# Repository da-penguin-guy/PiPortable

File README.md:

# PiPortable

This is a project that is designed to shove a CM5, a huge battery, and the pi touchscreen into a handheld form-factor. This is meant to help with troubleshooting for audio engineers, although the code is being designed to be very open, allowing you to add your own apps to the launcher and create custom IO Cards

# Source Code
The code can be found in the folder labeled "Source Code." Good luck.

# PCB Design Files
¯\_(ツ)_/¯

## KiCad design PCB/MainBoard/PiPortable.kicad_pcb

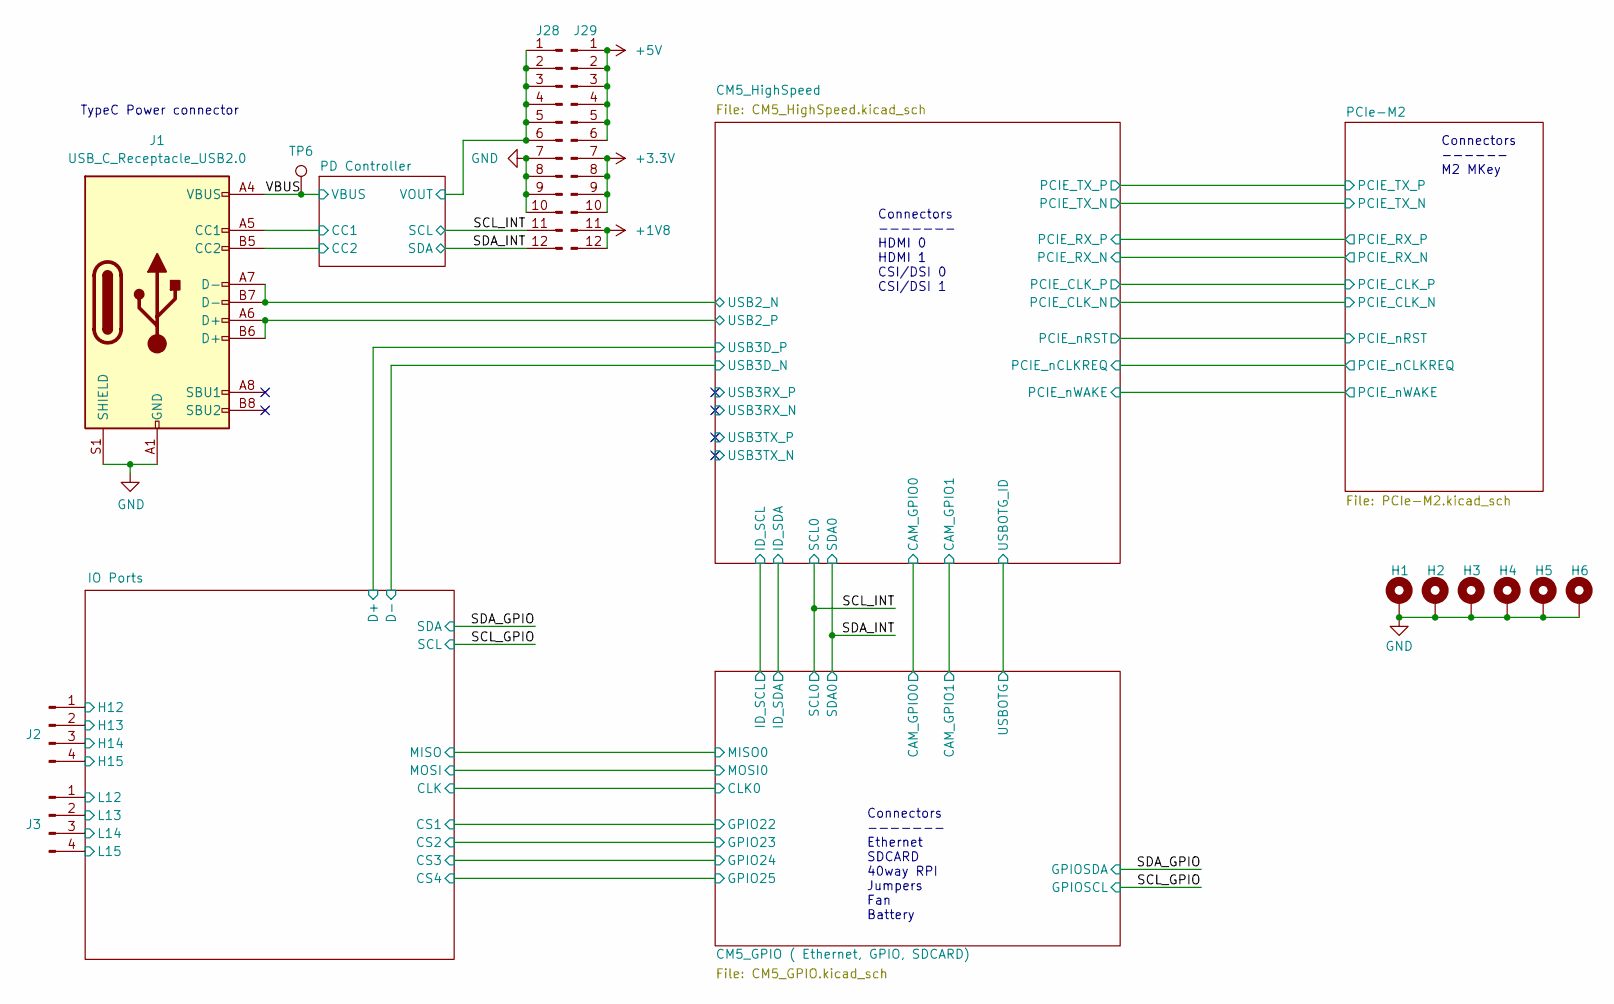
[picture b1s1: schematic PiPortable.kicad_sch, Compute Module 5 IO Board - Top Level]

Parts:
H1, H2, H3, H4, H5, H6: MountingHole_Pad; MountingHole_2.7mm_M2.5_DIN965_Pad
J1: USB_C_Receptacle_USB2.0; USB_C_Receptacle_Amphenol_12401548E4-2A; Part Description USBC USB2 data and power connector
J2, J3: Conn_01x04_Pin; PinHeader_1x04_P1.27mm_Vertical
J28, J29: Conn_01x12_Pin; PinHeader_1x12_P1.27mm_Vertical
TP6: TestPoint; TestPoint_Pad_D3.0mm

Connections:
+1V8: J29.11, J29.12; also elsewhere on the board
+3.3V: J29.7, J29.8, J29.9, J29.10; also elsewhere on the board
+5V: J29.1, J29.2, J29.3, J29.4, J29.5, J29.6; also elsewhere on the board
/CM5_HighSpeed/USB2_N: J1.A7 (D-), J1.B7 (D-); also elsewhere on the board
/CM5_HighSpeed/USB2_P: J1.A6 (D+), J1.B6 (D+); also elsewhere on the board
/IO Ports/H12: J2.1; also elsewhere on the board
/IO Ports/H13: J2.2; also elsewhere on the board
/IO Ports/H14: J2.3; also elsewhere on the board
/IO Ports/H15: J2.4; also elsewhere on the board
/IO Ports/L12: J3.1; also elsewhere on the board
/IO Ports/L13: J3.2; also elsewhere on the board
/IO Ports/L14: J3.3; also elsewhere on the board
/IO Ports/L15: J3.4; also elsewhere on the board
/PD Controller/CC1: J1.A5 (CC1); also elsewhere on the board
/PD Controller/CC2: J1.B5 (CC2); also elsewhere on the board
/PD Controller/VOUT: J28.1, J28.2, J28.3, J28.4, J28.5, J28.6; also elsewhere on the board
/SCL_INT: J28.11; also elsewhere on the board
/SDA_INT: J28.12; also elsewhere on the board
/VBUS: J1.A4 (VBUS), J1.A9 (VBUS), J1.B4 (VBUS), J1.B9 (VBUS), TP6.1; also elsewhere on the board
GND: H1.1, H2.1, H3.1, H4.1, H5.1, H6.1, J1.A1 (GND), J1.A12 (GND), J1.B1 (GND), J1.B12 (GND), J1.S1 (SHIELD), J28.7, J28.8, J28.9, J28.10; also elsewhere on the board

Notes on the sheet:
Connectors ------- Ethernet SDCARD 40way RPI Jumpers Fan Battery
Connectors ------ M2 MKey
TypeC Power connector
Connectors ------- HDMI 0 HDMI 1 CSI/DSI 0 CSI/DSI 1

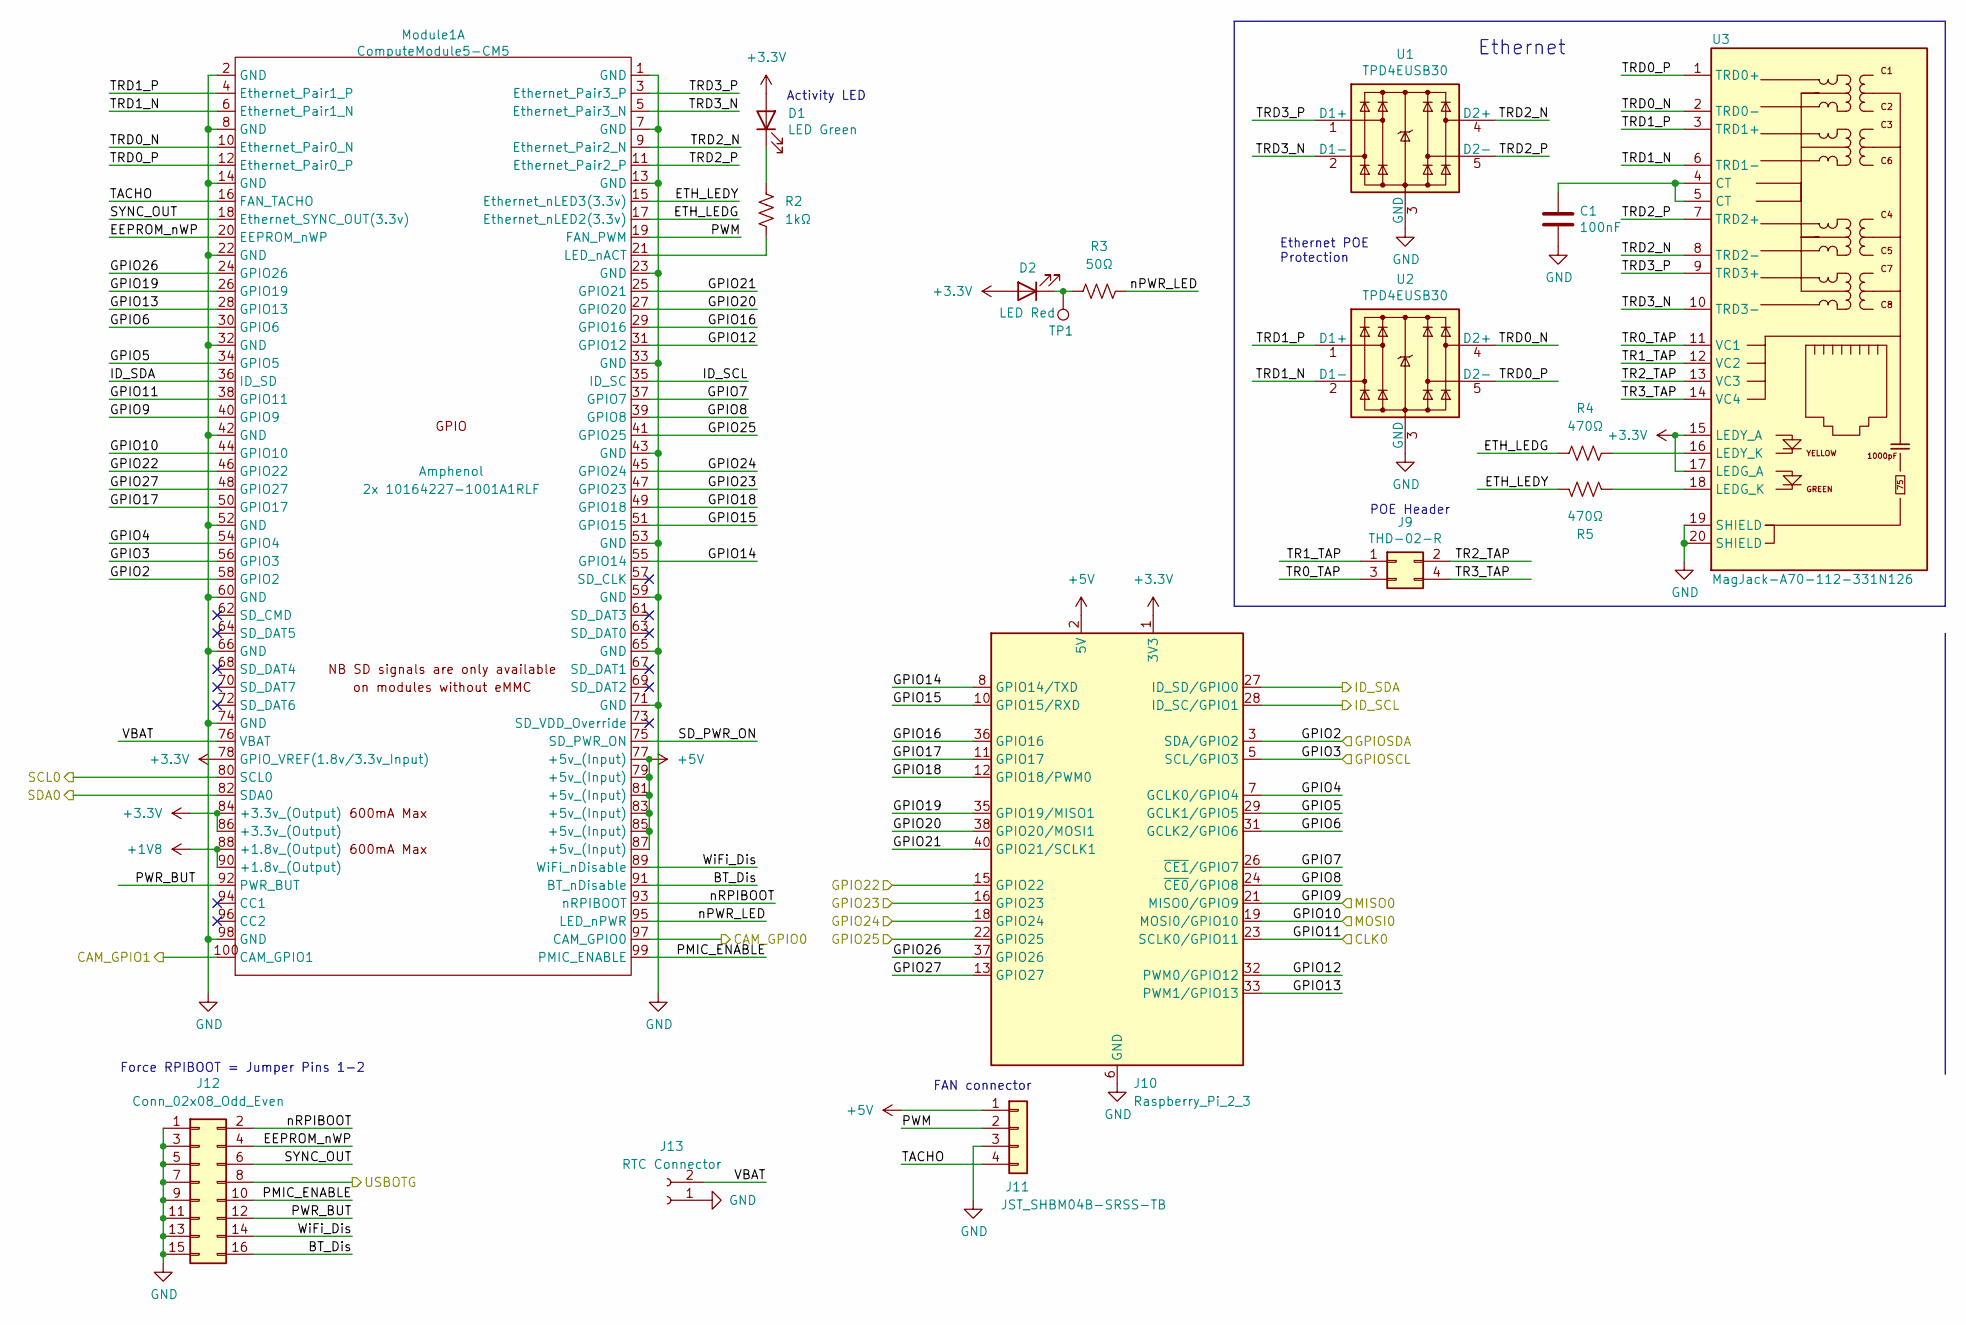
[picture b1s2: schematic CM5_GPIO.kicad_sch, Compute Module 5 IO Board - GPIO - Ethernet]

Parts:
C1: 100nF; C_0402_1005Metric_Pad0.74x0.62mm_HandSolder; Part Description 0.1uF 10% 16V Ceramic Capacitor X7R 040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
D1: LED Green; LED_0603_1608Metric; Part Description Green 572nm LED Indication - Discrete 2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
D2: LED Red; LED_0603_1608Metric; Part Description Red 620nm LED Indication - Discrete 2.2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
J9: THD-02-R; PinHeader_2x02_P2.54mm_Vertical; Part Description PinHeader_2x02_P2.54mm_Vertical
J10: Raspberry_Pi_2_3; PinHeader_2x20_P2.54mm_Vertical
J11: JST_SHBM04B-SRSS-TB; JST_SH_BM04B-SRSS-TB_1x04-1MP_P1.00mm_Vertical; Part Description 4 pin vertical 1mm pitch connector
J12: Conn_02x08_Odd_Even; PinHeader_2x08_P1.27mm_Vertical
J13: RTC Connector; JST_EH_B2B-EH-A_1x02_P2.50mm_Vertical
Module1: ComputeModule5-CM5; Raspberry-Pi-5-Compute-Module; Part Description 100 Position Connector Receptacle, Cent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
R2: 1kΩ; R_0402_1005Metric_Pad0.72x0.64mm_HandSolder
R3: 50Ω; R_0402_1005Metric_Pad0.72x0.64mm_HandSolder
R4, R5: 470Ω; R_0402_1005Metric_Pad0.72x0.64mm_HandSolder
TP1: TestPoint; TestPoint_Pad_2.0x2.0mm; Part Description Test point
U1, U2: TPD4EUSB30; USON-10_2.5x1.0mm_P0.5mm; Part Description Quad TVS diode for high speed signals (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
U3: MagJack-A70-112-331N126; TRJG0926HENL; Part Description Gigabit Ethernet Magjack

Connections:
+1V8: Module1.88 (+1.8v_(Output)), Module1.90 (+1.8v_(Output)); also elsewhere on the board
+3.3V: D1.2 (A), D2.2 (A), J10.1 (3V3), J10.17 (3V3), Module1.78 (GPIO_VREF(1.8v/3.3v_Input)), Module1.84 (+3.3v_(Output)), Module1.86 (+3.3v_(Output)), U3.15 (LEDY_A), U3.17 (LEDG_A); also elsewhere on the board
+5V: J10.2 (5V), J10.4 (5V), J11.1, Module1.77 (+5v_(Input)), Module1.79 (+5v_(Input)), Module1.81 (+5v_(Input)), Module1.83 (+5v_(Input)), Module1.85 (+5v_(Input)), Module1.87 (+5v_(Input)); also elsewhere on the board
/CM5_GPIO ( Ethernet, GPIO, SDCARD)/BT_Dis: J12.16, Module1.91 (BT_nDisable)
/CM5_GPIO ( Ethernet, GPIO, SDCARD)/CAM_GPIO0: Module1.97 (CAM_GPIO0); also elsewhere on the board
/CM5_GPIO ( Ethernet, GPIO, SDCARD)/CAM_GPIO1: Module1.100 (CAM_GPIO1); also elsewhere on the board
/CM5_GPIO ( Ethernet, GPIO, SDCARD)/EEPROM_nWP: J12.4, Module1.20 (EEPROM_nWP)
/CM5_GPIO ( Ethernet, GPIO, SDCARD)/ETH_LEDG: Module1.17 (Ethernet_nLED2(3.3v)), R4.1
/CM5_GPIO ( Ethernet, GPIO, SDCARD)/ETH_LEDY: Module1.15 (Ethernet_nLED3(3.3v)), R5.1
/CM5_GPIO ( Ethernet, GPIO, SDCARD)/GPIO4: J10.7 (GCLK0/GPIO4), Module1.54 (GPIO4)
/CM5_GPIO ( Ethernet, GPIO, SDCARD)/GPIO5: J10.29 (GCLK1/GPIO5), Module1.34 (GPIO5)
/CM5_GPIO ( Ethernet, GPIO, SDCARD)/GPIO6: J10.31 (GCLK2/GPIO6), Module1.30 (GPIO6)
/CM5_GPIO ( Ethernet, GPIO, SDCARD)/GPIO7: J10.26 (~CE1/GPIO7), Module1.37 (GPIO7)
/CM5_GPIO ( Ethernet, GPIO, SDCARD)/GPIO8: J10.24 (~CE0/GPIO8), Module1.39 (GPIO8)
/CM5_GPIO ( Ethernet, GPIO, SDCARD)/GPIO9: J10.21 (MISO0/GPIO9), Module1.40 (GPIO9); also elsewhere on the board
/CM5_GPIO ( Ethernet, GPIO, SDCARD)/GPIO10: J10.19 (MOSI0/GPIO10), Module1.44 (GPIO10); also elsewhere on the board
/CM5_GPIO ( Ethernet, GPIO, SDCARD)/GPIO11: J10.23 (SCLK0/GPIO11), Module1.38 (GPIO11); also elsewhere on the board
/CM5_GPIO ( Ethernet, GPIO, SDCARD)/GPIO12: J10.32 (PWM0/GPIO12), Module1.31 (GPIO12)
/CM5_GPIO ( Ethernet, GPIO, SDCARD)/GPIO13: J10.33 (PWM1/GPIO13), Module1.28 (GPIO13)
/CM5_GPIO ( Ethernet, GPIO, SDCARD)/GPIO14: J10.8 (GPIO14/TXD), Module1.55 (GPIO14)
/CM5_GPIO ( Ethernet, GPIO, SDCARD)/GPIO15: J10.10 (GPIO15/RXD), Module1.51 (GPIO15)
/CM5_GPIO ( Ethernet, GPIO, SDCARD)/GPIO16: J10.36 (GPIO16), Module1.29 (GPIO16)
/CM5_GPIO ( Ethernet, GPIO, SDCARD)/GPIO17: J10.11 (GPIO17), Module1.50 (GPIO17)
/CM5_GPIO ( Ethernet, GPIO, SDCARD)/GPIO18: J10.12 (GPIO18/PWM0), Module1.49 (GPIO18)
/CM5_GPIO ( Ethernet, GPIO, SDCARD)/GPIO19: J10.35 (GPIO19/MISO1), Module1.26 (GPIO19)
/CM5_GPIO ( Ethernet, GPIO, SDCARD)/GPIO20: J10.38 (GPIO20/MOSI1), Module1.27 (GPIO20)
/CM5_GPIO ( Ethernet, GPIO, SDCARD)/GPIO21: J10.40 (GPIO21/SCLK1), Module1.25 (GPIO21)
/CM5_GPIO ( Ethernet, GPIO, SDCARD)/GPIO22: J10.15 (GPIO22), Module1.46 (GPIO22); also elsewhere on the board
/CM5_GPIO ( Ethernet, GPIO, SDCARD)/GPIO23: J10.16 (GPIO23), Module1.47 (GPIO23); also elsewhere on the board
/CM5_GPIO ( Ethernet, GPIO, SDCARD)/GPIO24: J10.18 (GPIO24), Module1.45 (GPIO24); also elsewhere on the board
/CM5_GPIO ( Ethernet, GPIO, SDCARD)/GPIO25: J10.22 (GPIO25), Module1.41 (GPIO25); also elsewhere on the board
/CM5_GPIO ( Ethernet, GPIO, SDCARD)/GPIO26: J10.37 (GPIO26), Module1.24 (GPIO26)
/CM5_GPIO ( Ethernet, GPIO, SDCARD)/GPIO27: J10.13 (GPIO27), Module1.48 (GPIO27)
/CM5_GPIO ( Ethernet, GPIO, SDCARD)/ID_SCL: J10.28 (ID_SC/GPIO1), Module1.35 (ID_SC)
/CM5_GPIO ( Ethernet, GPIO, SDCARD)/ID_SDA: J10.27 (ID_SD/GPIO0), Module1.36 (ID_SD)
/CM5_GPIO ( Ethernet, GPIO, SDCARD)/PMIC_ENABLE: J12.10, Module1.99 (PMIC_ENABLE)
/CM5_GPIO ( Ethernet, GPIO, SDCARD)/PWM: J11.2, Module1.19 (FAN_PWM)
/CM5_GPIO ( Ethernet, GPIO, SDCARD)/PWR_BUT: J12.12, Module1.92 (PWR_BUT)
/CM5_GPIO ( Ethernet, GPIO, SDCARD)/SD_PWR_ON: Module1.75 (SD_PWR_ON)
/CM5_GPIO ( Ethernet, GPIO, SDCARD)/SYNC_OUT: J12.6, Module1.18 (Ethernet_SYNC_OUT(3.3v))
/CM5_GPIO ( Ethernet, GPIO, SDCARD)/TACHO: J11.4, Module1.16 (FAN_TACHO)
/CM5_GPIO ( Ethernet, GPIO, SDCARD)/TR0_TAP: J9.3, U3.11 (VC1)
/CM5_GPIO ( Ethernet, GPIO, SDCARD)/TR1_TAP: J9.1, U3.12 (VC2)
/CM5_GPIO ( Ethernet, GPIO, SDCARD)/TR2_TAP: J9.2, U3.13 (VC3)
/CM5_GPIO ( Ethernet, GPIO, SDCARD)/TR3_TAP: J9.4, U3.14 (VC4)
/CM5_GPIO ( Ethernet, GPIO, SDCARD)/TRD0_N: Module1.10 (Ethernet_Pair0_N), U2.4 (D2+), U2.7, U3.2 (TRD0-)
/CM5_GPIO ( Ethernet, GPIO, SDCARD)/TRD0_P: Module1.12 (Ethernet_Pair0_P), U2.5 (D2-), U2.6, U3.1 (TRD0+)
/CM5_GPIO ( Ethernet, GPIO, SDCARD)/TRD1_N: Module1.6 (Ethernet_Pair1_N), U2.2 (D1-), U2.9, U3.6 (TRD1-)
/CM5_GPIO ( Ethernet, GPIO, SDCARD)/TRD1_P: Module1.4 (Ethernet_Pair1_P), U2.1 (D1+), U2.10, U3.3 (TRD1+)
/CM5_GPIO ( Ethernet, GPIO, SDCARD)/TRD2_N: Module1.9 (Ethernet_Pair2_N), U1.4 (D2+), U1.7, U3.8 (TRD2-)
/CM5_GPIO ( Ethernet, GPIO, SDCARD)/TRD2_P: Module1.11 (Ethernet_Pair2_P), U1.5 (D2-), U1.6, U3.7 (TRD2+)
/CM5_GPIO ( Ethernet, GPIO, SDCARD)/TRD3_N: Module1.5 (Ethernet_Pair3_N), U1.2 (D1-), U1.9, U3.10 (TRD3-)
/CM5_GPIO ( Ethernet, GPIO, SDCARD)/TRD3_P: Module1.3 (Ethernet_Pair3_P), U1.1 (D1+), U1.10, U3.9 (TRD3+)
/CM5_GPIO ( Ethernet, GPIO, SDCARD)/USBOTG: J12.8; also elsewhere on the board
/CM5_GPIO ( Ethernet, GPIO, SDCARD)/VBAT: J13.2, Module1.76 (VBAT)
/CM5_GPIO ( Ethernet, GPIO, SDCARD)/WiFi_Dis: J12.14, Module1.89 (WiFi_nDisable)
/CM5_GPIO ( Ethernet, GPIO, SDCARD)/nPWR_LED: Module1.95 (LED_nPWR), R3.2
/CM5_GPIO ( Ethernet, GPIO, SDCARD)/nRPIBOOT: J12.2, Module1.93 (nRPIBOOT)
/SCL_GPIO: J10.5 (SCL/GPIO3), Module1.56 (GPIO3); also elsewhere on the board
/SCL_INT: Module1.80 (SCL0); also elsewhere on the board
/SDA_GPIO: J10.3 (SDA/GPIO2), Module1.58 (GPIO2); also elsewhere on the board
/SDA_INT: Module1.82 (SDA0); also elsewhere on the board
GND: C1.2, J10.6 (GND), J10.9 (GND), J10.14 (GND), J10.20 (GND), J10.25 (GND), J10.30 (GND), J10.34 (GND), J10.39 (GND), J11.3, J12.1, J12.3, J12.5, J12.7, J12.9, J12.11, J12.13, J12.15, J13.1, Module1.1 (GND), Module1.2 (GND), Module1.7 (GND), Module1.8 (GND), Module1.13 (GND), Module1.14 (GND), Module1.22 (GND), Module1.23 (GND), Module1.32 (GND), Module1.33 (GND), Module1.42 (GND), Module1.43 (GND), Module1.52 (GND), Module1.53 (GND), Module1.59 (GND), Module1.60 (GND), Module1.65 (GND), Module1.66 (GND), Module1.71 (GND), Module1.74 (GND), Module1.98 (GND), U1.3 (GND), U1.8 (GND), U2.3 (GND), U2.8 (GND), U3.19 (SHIELD), U3.20 (SHIELD); also elsewhere on the board
unnamed: C1.1, U3.4 (CT), U3.5 (CT)
unnamed: D1.1 (K), R2.2
unnamed: D2.1 (K), R3.1, TP1.1
unnamed: Module1.21 (LED_nACT), R2.1
unnamed: R5.2, U3.18 (LEDG_K)
unnamed: R4.2, U3.16 (LEDY_K)

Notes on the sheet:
Activity LED
FAN connector
Ethernet POE Protection
POE Header
Force RPIBOOT = Jumper Pins 1-2
Ethernet

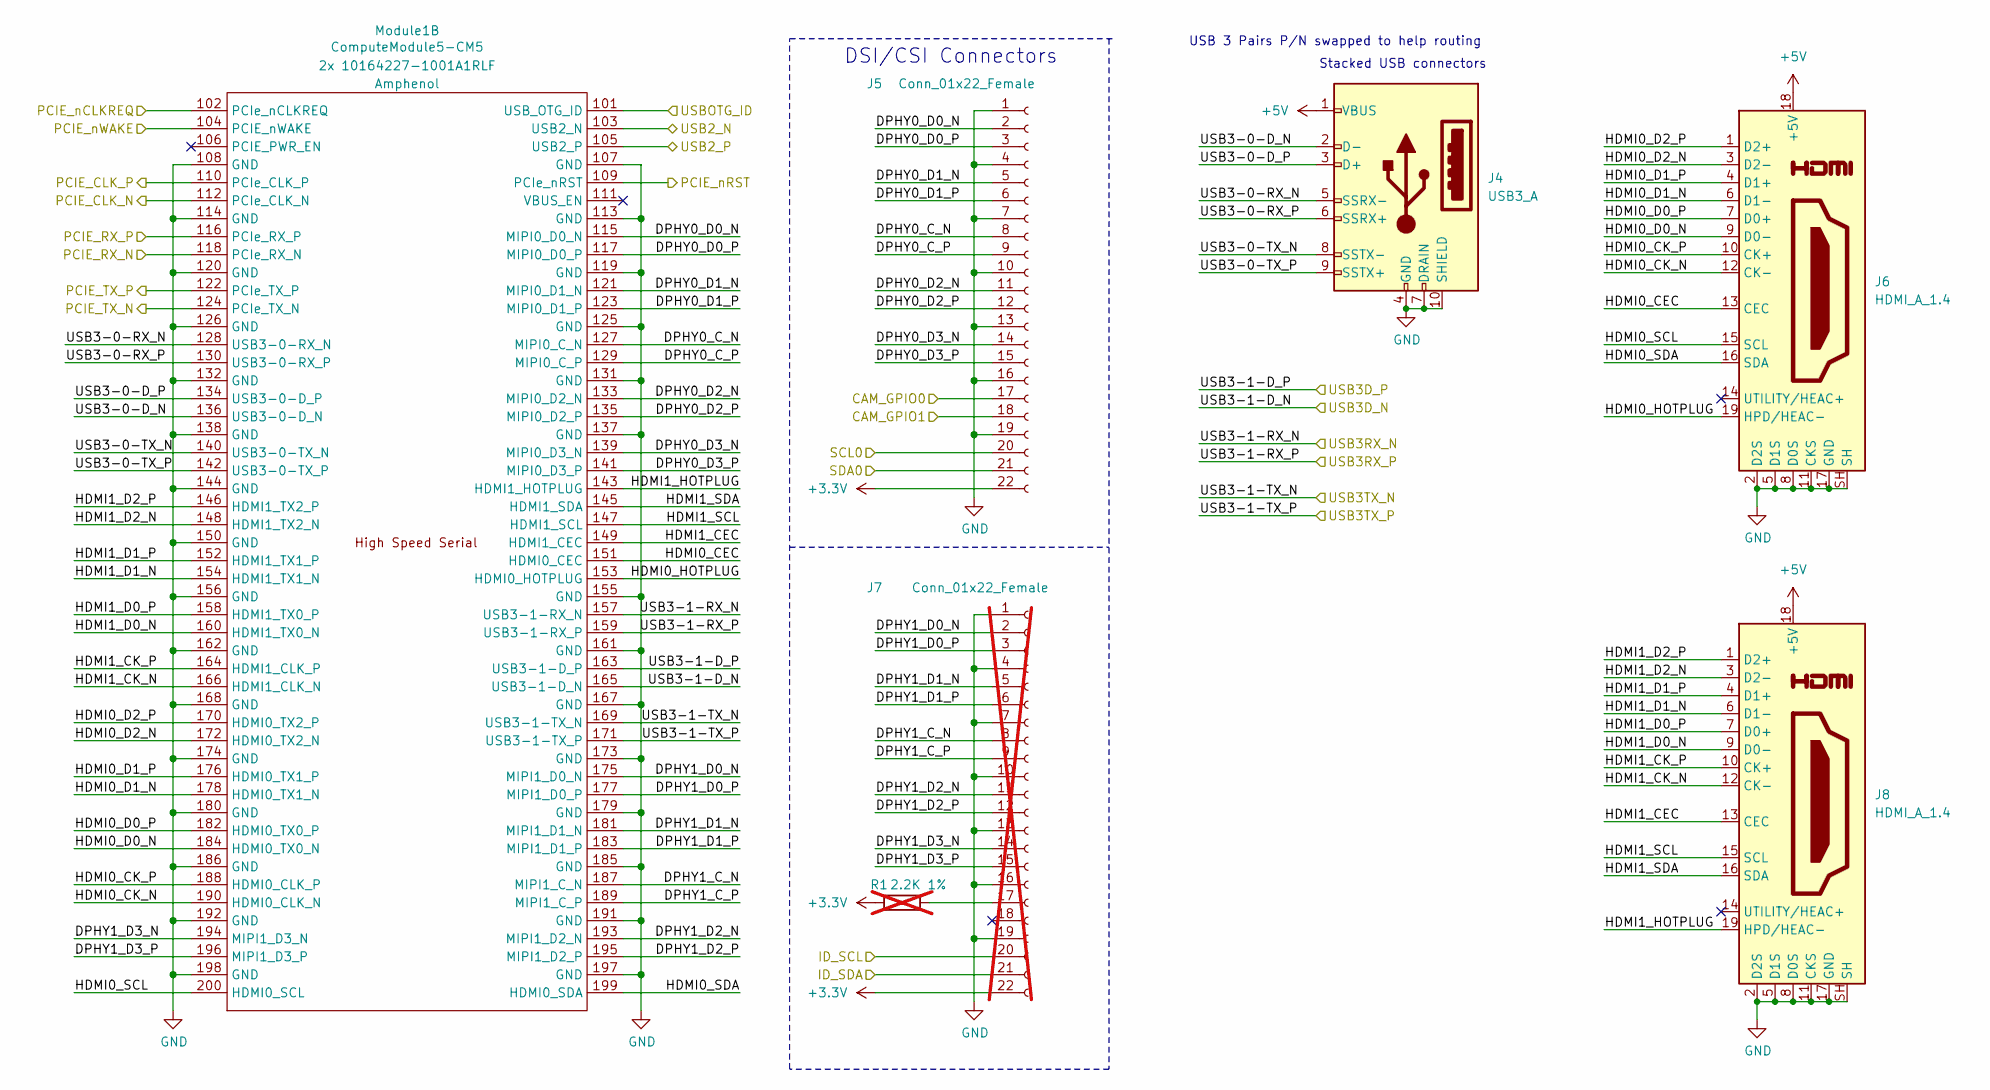
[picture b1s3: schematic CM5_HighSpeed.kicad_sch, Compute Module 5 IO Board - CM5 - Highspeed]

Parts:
J4: USB3_A; USB3_A_Molex_48393-001
J5: Conn_01x22_Female; Hirose_FH12-22S-0.5SH_1x22-1MP_P0.50mm_Horizontal; Part Description 22 Position FFC, FPC Connector Contacts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
J6, J8: HDMI_A_1.4; HDMI_A_Molex_208658-1001_Horizontal
J7: Conn_01x22_Female; Hirose_FH12-22S-0.5SH_1x22-1MP_P0.50mm_Horizontal; Part Description 22 Position FFC, FPC Connector Contacts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; not fitted
Module1: ComputeModule5-CM5; Raspberry-Pi-5-Compute-Module; Part Description 100 Position Connector Receptacle, Cent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
R1: 2.2K 1%; R_0603_1608Metric_Pad0.98x0.95mm_HandSolder; Part Description Resistor 2.2K M1005 1% 63mW; not fitted

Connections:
+3.3V: J5.22, J7.22, R1.1; also elsewhere on the board
+5V: J4.1 (VBUS), J6.18 (+5V), J8.18 (+5V); also elsewhere on the board
/CM5_GPIO ( Ethernet, GPIO, SDCARD)/CAM_GPIO0: J5.17; also elsewhere on the board
/CM5_GPIO ( Ethernet, GPIO, SDCARD)/CAM_GPIO1: J5.18; also elsewhere on the board
/CM5_GPIO ( Ethernet, GPIO, SDCARD)/USBOTG: Module1.101 (USB_OTG_ID); also elsewhere on the board
/CM5_HighSpeed/DPHY0_C_N: J5.8, Module1.127 (MIPI0_C_N)
/CM5_HighSpeed/DPHY0_C_P: J5.9, Module1.129 (MIPI0_C_P)
/CM5_HighSpeed/DPHY0_D0_N: J5.2, Module1.115 (MIPI0_D0_N)
/CM5_HighSpeed/DPHY0_D0_P: J5.3, Module1.117 (MIPI0_D0_P)
/CM5_HighSpeed/DPHY0_D1_N: J5.5, Module1.121 (MIPI0_D1_N)
/CM5_HighSpeed/DPHY0_D1_P: J5.6, Module1.123 (MIPI0_D1_P)
/CM5_HighSpeed/DPHY0_D2_N: J5.11, Module1.133 (MIPI0_D2_N)
/CM5_HighSpeed/DPHY0_D2_P: J5.12, Module1.135 (MIPI0_D2_P)
/CM5_HighSpeed/DPHY0_D3_N: J5.14, Module1.139 (MIPI0_D3_N)
/CM5_HighSpeed/DPHY0_D3_P: J5.15, Module1.141 (MIPI0_D3_P)
/CM5_HighSpeed/DPHY1_C_N: J7.8, Module1.187 (MIPI1_C_N)
/CM5_HighSpeed/DPHY1_C_P: J7.9, Module1.189 (MIPI1_C_P)
/CM5_HighSpeed/DPHY1_D0_N: J7.2, Module1.175 (MIPI1_D0_N)
/CM5_HighSpeed/DPHY1_D0_P: J7.3, Module1.177 (MIPI1_D0_P)
/CM5_HighSpeed/DPHY1_D1_N: J7.5, Module1.181 (MIPI1_D1_N)
/CM5_HighSpeed/DPHY1_D1_P: J7.6, Module1.183 (MIPI1_D1_P)
/CM5_HighSpeed/DPHY1_D2_N: J7.11, Module1.193 (MIPI1_D2_N)
/CM5_HighSpeed/DPHY1_D2_P: J7.12, Module1.195 (MIPI1_D2_P)
/CM5_HighSpeed/DPHY1_D3_N: J7.14, Module1.194 (MIPI1_D3_N)
/CM5_HighSpeed/DPHY1_D3_P: J7.15, Module1.196 (MIPI1_D3_P)
/CM5_HighSpeed/HDMI0_CEC: J6.13 (CEC), Module1.151 (HDMI0_CEC)
/CM5_HighSpeed/HDMI0_CK_N: J6.12 (CK-), Module1.190 (HDMI0_CLK_N)
/CM5_HighSpeed/HDMI0_CK_P: J6.10 (CK+), Module1.188 (HDMI0_CLK_P)
/CM5_HighSpeed/HDMI0_D0_N: J6.9 (D0-), Module1.184 (HDMI0_TX0_N)
/CM5_HighSpeed/HDMI0_D0_P: J6.7 (D0+), Module1.182 (HDMI0_TX0_P)
/CM5_HighSpeed/HDMI0_D1_N: J6.6 (D1-), Module1.178 (HDMI0_TX1_N)
/CM5_HighSpeed/HDMI0_D1_P: J6.4 (D1+), Module1.176 (HDMI0_TX1_P)
/CM5_HighSpeed/HDMI0_D2_N: J6.3 (D2-), Module1.172 (HDMI0_TX2_N)
/CM5_HighSpeed/HDMI0_D2_P: J6.1 (D2+), Module1.170 (HDMI0_TX2_P)
/CM5_HighSpeed/HDMI0_HOTPLUG: J6.19 (HPD/HEAC-), Module1.153 (HDMI0_HOTPLUG)
/CM5_HighSpeed/HDMI0_SCL: J6.15 (SCL), Module1.200 (HDMI0_SCL)
/CM5_HighSpeed/HDMI0_SDA: J6.16 (SDA), Module1.199 (HDMI0_SDA)
/CM5_HighSpeed/HDMI1_CEC: J8.13 (CEC), Module1.149 (HDMI1_CEC)
/CM5_HighSpeed/HDMI1_CK_N: J8.12 (CK-), Module1.166 (HDMI1_CLK_N)
/CM5_HighSpeed/HDMI1_CK_P: J8.10 (CK+), Module1.164 (HDMI1_CLK_P)
/CM5_HighSpeed/HDMI1_D0_N: J8.9 (D0-), Module1.160 (HDMI1_TX0_N)
/CM5_HighSpeed/HDMI1_D0_P: J8.7 (D0+), Module1.158 (HDMI1_TX0_P)
/CM5_HighSpeed/HDMI1_D1_N: J8.6 (D1-), Module1.154 (HDMI1_TX1_N)
/CM5_HighSpeed/HDMI1_D1_P: J8.4 (D1+), Module1.152 (HDMI1_TX1_P)
/CM5_HighSpeed/HDMI1_D2_N: J8.3 (D2-), Module1.148 (HDMI1_TX2_N)
/CM5_HighSpeed/HDMI1_D2_P: J8.1 (D2+), Module1.146 (HDMI1_TX2_P)
/CM5_HighSpeed/HDMI1_HOTPLUG: J8.19 (HPD/HEAC-), Module1.143 (HDMI1_HOTPLUG)
/CM5_HighSpeed/HDMI1_SCL: J8.15 (SCL), Module1.147 (HDMI1_SCL)
/CM5_HighSpeed/HDMI1_SDA: J8.16 (SDA), Module1.145 (HDMI1_SDA)
/CM5_HighSpeed/PCIE_CLK_N: Module1.112 (PCIe_CLK_N); also elsewhere on the board
/CM5_HighSpeed/PCIE_CLK_P: Module1.110 (PCIe_CLK_P); also elsewhere on the board
/CM5_HighSpeed/PCIE_RX_N: Module1.118 (PCIe_RX_N); also elsewhere on the board
/CM5_HighSpeed/PCIE_RX_P: Module1.116 (PCIe_RX_P); also elsewhere on the board
/CM5_HighSpeed/PCIE_TX_N: Module1.124 (PCIe_TX_N); also elsewhere on the board
/CM5_HighSpeed/PCIE_TX_P: Module1.122 (PCIe_TX_P); also elsewhere on the board
/CM5_HighSpeed/PCIE_nCLKREQ: Module1.102 (PCIe_nCLKREQ); also elsewhere on the board
/CM5_HighSpeed/PCIE_nRST: Module1.109 (PCIe_nRST); also elsewhere on the board
/CM5_HighSpeed/PCIE_nWAKE: Module1.104 (PCIE_nWAKE); also elsewhere on the board
/CM5_HighSpeed/USB2_N: Module1.103 (USB2_N); also elsewhere on the board
/CM5_HighSpeed/USB2_P: Module1.105 (USB2_P); also elsewhere on the board
/CM5_HighSpeed/USB3-0-D_N: J4.2 (D-), Module1.136 (USB3-0-D_N)
/CM5_HighSpeed/USB3-0-D_P: J4.3 (D+), Module1.134 (USB3-0-D_P)
/CM5_HighSpeed/USB3-0-RX_N: J4.5 (SSRX-), Module1.128 (USB3-0-RX_N)
/CM5_HighSpeed/USB3-0-RX_P: J4.6 (SSRX+), Module1.130 (USB3-0-RX_P)
/CM5_HighSpeed/USB3-0-TX_N: J4.8 (SSTX-), Module1.140 (USB3-0-TX_N)
/CM5_HighSpeed/USB3-0-TX_P: J4.9 (SSTX+), Module1.142 (USB3-0-TX_P)
/CM5_HighSpeed/USB3-1-D_N: Module1.165 (USB3-1-D_N); also elsewhere on the board
/CM5_HighSpeed/USB3-1-D_P: Module1.163 (USB3-1-D_P); also elsewhere on the board
/CM5_HighSpeed/USB3-1-RX_N: Module1.157 (USB3-1-RX_N)
/CM5_HighSpeed/USB3-1-RX_P: Module1.159 (USB3-1-RX_P)
/CM5_HighSpeed/USB3-1-TX_N: Module1.169 (USB3-1-TX_N)
/CM5_HighSpeed/USB3-1-TX_P: Module1.171 (USB3-1-TX_P)
/SCL_INT: J5.20; also elsewhere on the board
/SDA_INT: J5.21; also elsewhere on the board
GND: J4.4 (GND), J4.7 (DRAIN), J4.10 (SHIELD), J5.1, J5.4, J5.7, J5.10, J5.13, J5.16, J5.19, J6.2 (D2S), J6.5 (D1S), J6.8 (D0S), J6.11 (CKS), J6.17 (GND), J6.SH, J7.1, J7.4, J7.7, J7.10, J7.13, J7.16, J7.19, J8.2 (D2S), J8.5 (D1S), J8.8 (D0S), J8.11 (CKS), J8.17 (GND), J8.SH, Module1.107 (GND), Module1.108 (GND), Module1.113 (GND), Module1.114 (GND), Module1.119 (GND), Module1.120 (GND), Module1.125 (GND), Module1.126 (GND), Module1.131 (GND), Module1.132 (GND), Module1.137 (GND), Module1.138 (GND), Module1.144 (GND), Module1.150 (GND), Module1.155 (GND), Module1.156 (GND), Module1.161 (GND), Module1.162 (GND), Module1.167 (GND), Module1.168 (GND), Module1.173 (GND), Module1.174 (GND), Module1.179 (GND), Module1.180 (GND), Module1.185 (GND), Module1.186 (GND), Module1.191 (GND), Module1.192 (GND), Module1.197 (GND), Module1.198 (GND); also elsewhere on the board
unnamed: J7.17, R1.2

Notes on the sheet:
USB 3 Pairs P/N swapped to help routing
DSI/CSI Connectors
Stacked USB connectors

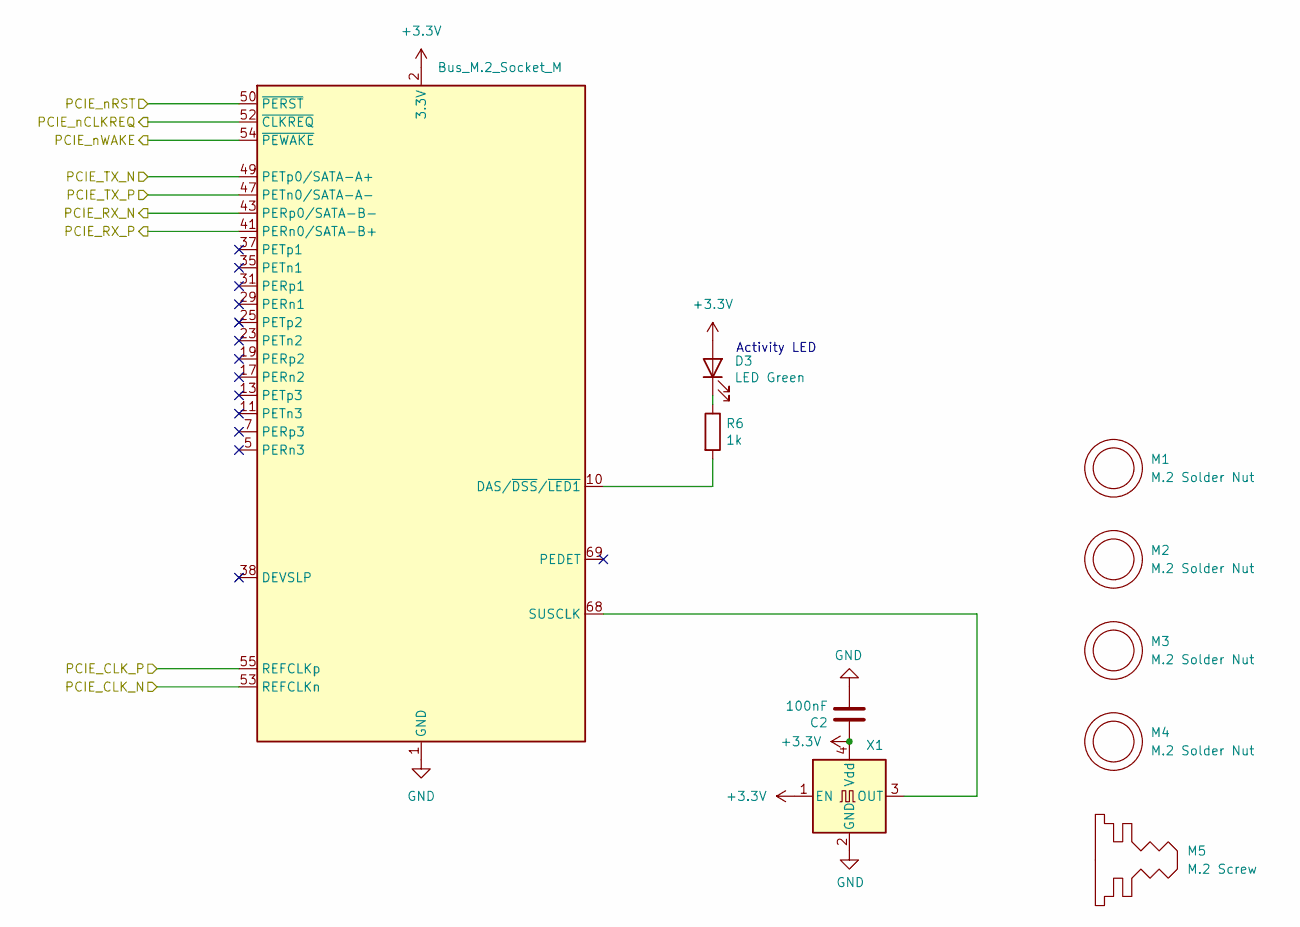
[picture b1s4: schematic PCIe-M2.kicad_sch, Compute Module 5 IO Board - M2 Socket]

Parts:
C2: 100nF; C_0603_1608Metric_Pad1.08x0.95mm_HandSolder; Part Description 0.1uF 10% 16V Ceramic Capacitor X7R 040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
D3: LED Green; LED_0603_1608Metric; Part Description Green 572nm LED Indication - Discrete 2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
J14: Bus_M.2_Socket_M; M.2 M Key socket
M1, M2, M3, M4: M.2 Solder Nut; Part Description Solder nut for M.2 slot
M5: M.2 Screw; Part Description M.2 Screw
R6: 1k; R_0402_1005Metric_Pad0.72x0.64mm_HandSolder; Part Description Resistor 1K M1005 1% 63mW
X1: ASEK-32.768KHZ-L-R-T; Oscillator_SMD_Abracon_ASE-4Pin_3.2x2.5mm

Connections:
+3.3V: C2.1, D3.2 (A), J14.2 (3.3V), J14.4 (3.3V), J14.12 (3.3V), J14.14 (3.3V), J14.16 (3.3V), J14.18 (3.3V), J14.70 (3.3V), J14.72 (3.3V), J14.74 (3.3V), X1.1 (EN), X1.4 (Vdd); also elsewhere on the board
/CM5_HighSpeed/PCIE_CLK_N: J14.53 (REFCLKn); also elsewhere on the board
/CM5_HighSpeed/PCIE_CLK_P: J14.55 (REFCLKp); also elsewhere on the board
/CM5_HighSpeed/PCIE_RX_N: J14.43 (PERp0/SATA-B-); also elsewhere on the board
/CM5_HighSpeed/PCIE_RX_P: J14.41 (PERn0/SATA-B+); also elsewhere on the board
/CM5_HighSpeed/PCIE_TX_N: J14.49 (PETp0/SATA-A+); also elsewhere on the board
/CM5_HighSpeed/PCIE_TX_P: J14.47 (PETn0/SATA-A-); also elsewhere on the board
/CM5_HighSpeed/PCIE_nCLKREQ: J14.52 (~CLKREQ); also elsewhere on the board
/CM5_HighSpeed/PCIE_nRST: J14.50 (~PERST); also elsewhere on the board
/CM5_HighSpeed/PCIE_nWAKE: J14.54 (~PEWAKE); also elsewhere on the board
GND: C2.2, J14.1 (GND), J14.3 (GND), J14.9 (GND), J14.15 (GND), J14.21 (GND), J14.27 (GND), J14.33 (GND), J14.39 (GND), J14.45 (GND), J14.51 (GND), J14.57 (GND), J14.71 (GND), J14.73 (GND), J14.75 (GND), X1.2 (GND); also elsewhere on the board
unnamed: D3.1 (K), R6.1
unnamed: J14.10 (DAS/~DSS/~LED1), R6.2
unnamed: J14.68 (SUSCLK), X1.3 (OUT)

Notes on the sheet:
Activity LED

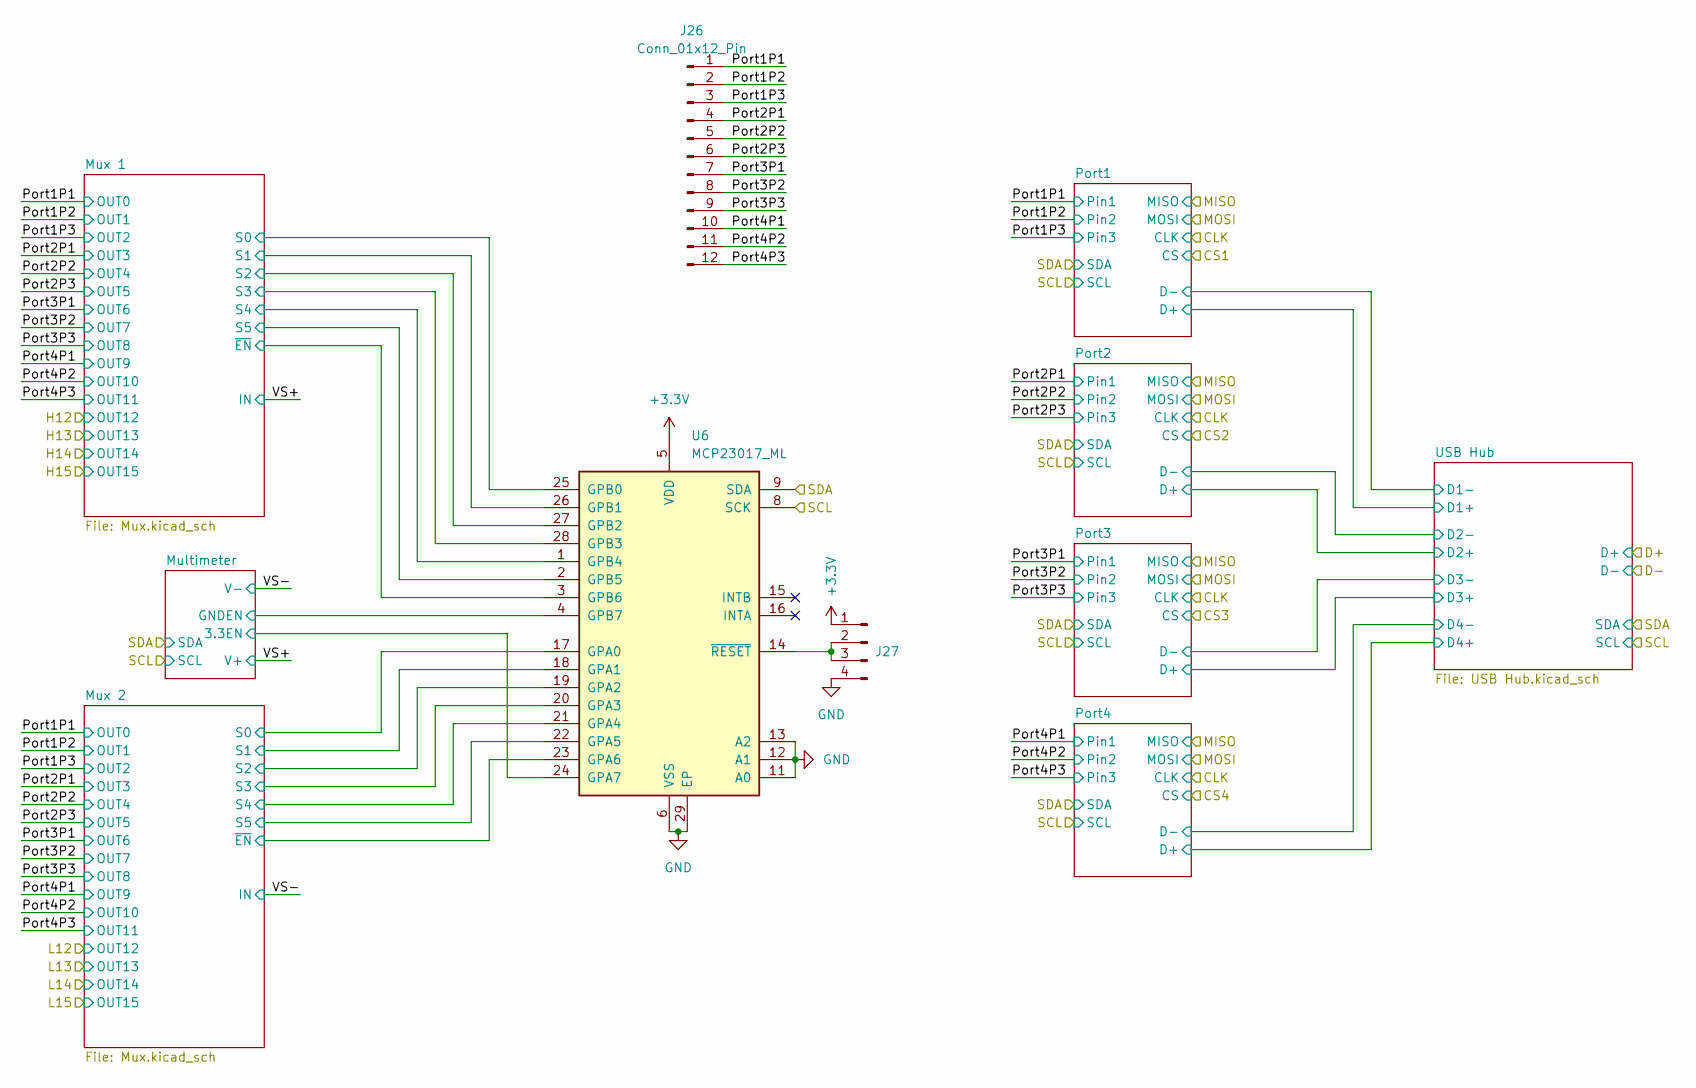
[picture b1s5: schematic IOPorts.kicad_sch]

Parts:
J26: Conn_01x12_Pin; PinHeader_1x12_P1.27mm_Vertical
J27: Conn_01x04_Pin; PinHeader_1x04_P1.27mm_Vertical
U6: MCP23017_ML; QFN-28-1EP_6x6mm_P0.65mm_EP4.25x4.25mm

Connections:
+3.3V: J27.1, U6.5 (VDD); also elsewhere on the board
/IO Ports/Multimeter/3.3EN: U6.24 (GPA7); also elsewhere on the board
/IO Ports/Multimeter/GNDEN: U6.4 (GPB7); also elsewhere on the board
/IO Ports/Mux 1/S0: U6.25 (GPB0); also elsewhere on the board
/IO Ports/Mux 1/S1: U6.26 (GPB1); also elsewhere on the board
/IO Ports/Mux 1/S2: U6.27 (GPB2); also elsewhere on the board
/IO Ports/Mux 1/S3: U6.28 (GPB3); also elsewhere on the board
/IO Ports/Mux 1/S4: U6.1 (GPB4); also elsewhere on the board
/IO Ports/Mux 1/S5: U6.2 (GPB5); also elsewhere on the board
/IO Ports/Mux 1/~EN: U6.3 (GPB6); also elsewhere on the board
/IO Ports/Mux 2/S0: U6.17 (GPA0); also elsewhere on the board
/IO Ports/Mux 2/S1: U6.18 (GPA1); also elsewhere on the board
/IO Ports/Mux 2/S2: U6.19 (GPA2); also elsewhere on the board
/IO Ports/Mux 2/S3: U6.20 (GPA3); also elsewhere on the board
/IO Ports/Mux 2/S4: U6.21 (GPA4); also elsewhere on the board
/IO Ports/Mux 2/S5: U6.22 (GPA5); also elsewhere on the board
/IO Ports/Mux 2/~EN: U6.23 (GPA6); also elsewhere on the board
/IO Ports/Port1P1: J26.1; also elsewhere on the board
/IO Ports/Port1P2: J26.2; also elsewhere on the board
/IO Ports/Port1P3: J26.3; also elsewhere on the board
/IO Ports/Port2P1: J26.4; also elsewhere on the board
/IO Ports/Port2P2: J26.5; also elsewhere on the board
/IO Ports/Port2P3: J26.6; also elsewhere on the board
/IO Ports/Port3P1: J26.7; also elsewhere on the board
/IO Ports/Port3P2: J26.8; also elsewhere on the board
/IO Ports/Port3P3: J26.9; also elsewhere on the board
/IO Ports/Port4P1: J26.10; also elsewhere on the board
/IO Ports/Port4P2: J26.11; also elsewhere on the board
/IO Ports/Port4P3: J26.12; also elsewhere on the board
/SCL_GPIO: U6.8 (SCK); also elsewhere on the board
/SDA_GPIO: U6.9 (SDA); also elsewhere on the board
GND: J27.4, U6.6 (VSS), U6.11 (A0), U6.12 (A1), U6.13 (A2), U6.29 (EP); also elsewhere on the board
unnamed: J27.2, J27.3, U6.14 (~RESET)

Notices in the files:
PCB/CM5_GPIO.kicad_sch:
Copyright © 2024 Raspberry Pi Ltd.
